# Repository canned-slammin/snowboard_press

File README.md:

# snowboard_press
 Zephyr implementation of heat and pressure controls

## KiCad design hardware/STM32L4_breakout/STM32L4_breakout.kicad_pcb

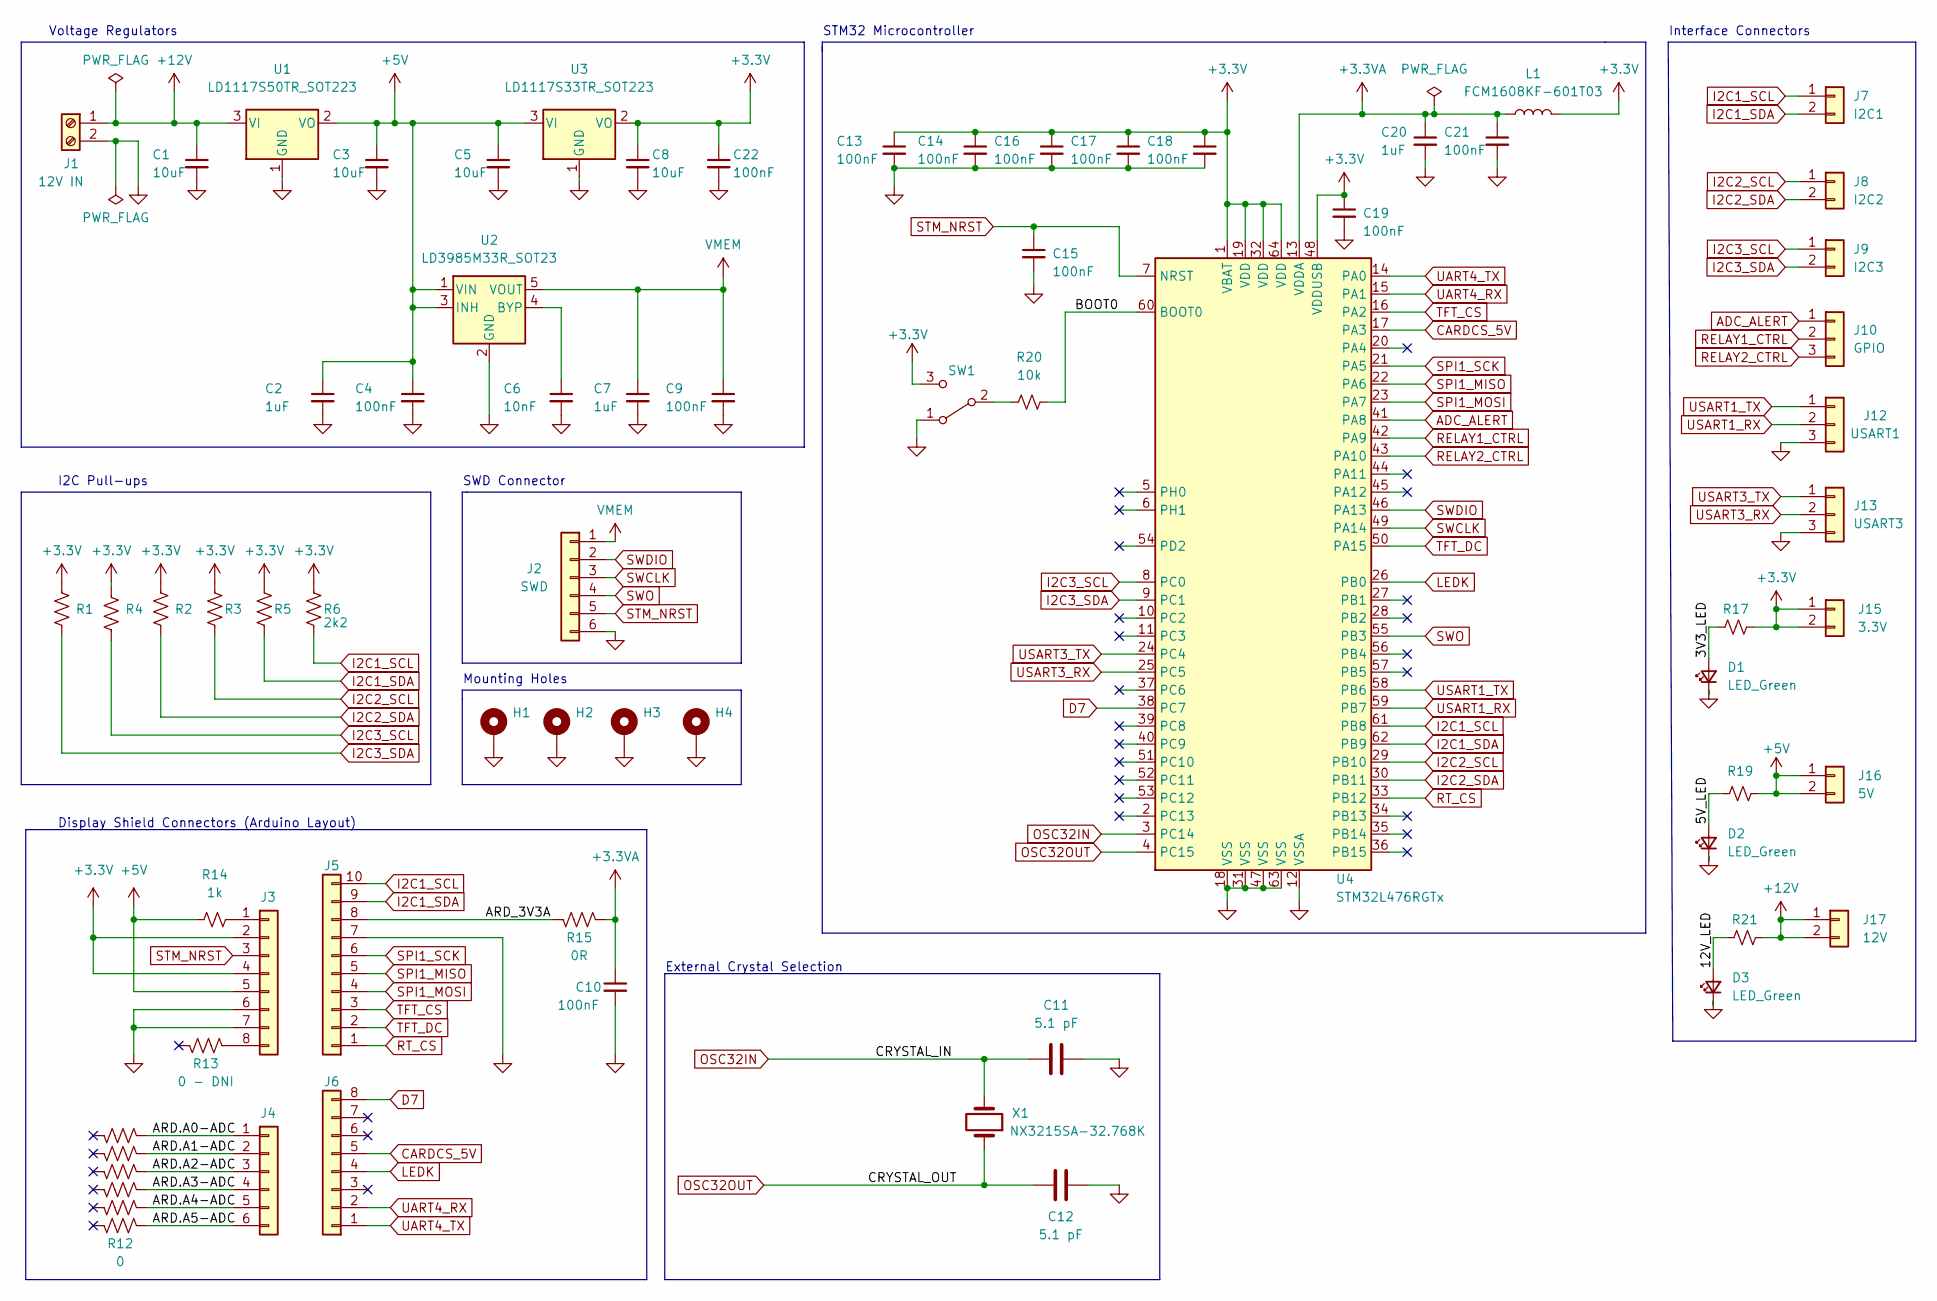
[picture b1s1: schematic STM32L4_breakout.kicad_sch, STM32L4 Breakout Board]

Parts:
C1, C3, C5, C8: 10uF; C_0805_2012Metric
C2, C7, C20: 1uF; C_0805_2012Metric
C4, C9, C10, C13, C14, C15, C16, C17, C18, C19, C21, C22: 100nF; C_0603_1608Metric
C6: 10nF; C_0603_1608Metric
C11, C12: 5.1 pF; C_0402_1005Metric
D1, D2, D3: LED_Green; LED_0603_1608Metric
H1, H2, H3, H4: MountingHole_Pad; MountingHole_3.2mm_M3_DIN965_Pad_TopOnly
J1: 12V IN; TerminalBlock_Phoenix_MKDS-1,5-2_1x02_P5.00mm_Horizontal
J2: SWD; PinHeader_1x06_P2.54mm_Vertical
J3, J6: Conn_01x08; PinSocket_1x08_P2.54mm_Vertical
J4: Conn_01x06; PinSocket_1x06_P2.54mm_Vertical
J5: Conn_01x10; PinSocket_1x10_P2.54mm_Vertical
J7: I2C1; PinHeader_1x02_P2.54mm_Vertical
J8: I2C2; PinHeader_1x02_P2.54mm_Vertical
J9: I2C3; PinHeader_1x02_P2.54mm_Vertical
J10: GPIO; PinSocket_1x03_P2.54mm_Vertical
J12: USART1; PinHeader_1x03_P2.54mm_Vertical
J13: USART3; PinHeader_1x03_P2.54mm_Vertical
J15: 3.3V; PinHeader_1x02_P2.54mm_Vertical
J16: 5V; PinHeader_1x02_P2.54mm_Vertical
J17: 12V; PinHeader_1x02_P2.54mm_Vertical
L1: FCM1608KF-601T03; L_0603_1608Metric
R1, R2, R3, R4, R5, R6: 2k2; R_0603_1608Metric
R7, R8, R9, R10, R11, R13: 0 - DNI; R_0603_1608Metric
R12: 0; R_0603_1608Metric
R14: 1k; R_0603_1608Metric
R15: 0R; R_0603_1608Metric
R17, R19, R21: 330R; R_0603_1608Metric
R20: 10k; R_0603_1608Metric
SW1: SW_SPDT; SW_SPDT_CK-JS102011SAQN
U1: LD1117S50TR_SOT223; SOT-223-3_TabPin2
U2: LD3985M33R_SOT23; SOT-23-5
U3: LD1117S33TR_SOT223; SOT-223-3_TabPin2
U4: STM32L476RGTx; LQFP-64_10x10mm_P0.5mm
X1: NX3215SA-32.768K; Crystal_SMD_3215-2Pin_3.2x1.5mm

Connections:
+3.3V: C8.1, C13.1, C14.1, C16.1, C17.1, C18.1, C19.1, C22.1, J3.2, J3.4, J15.1, J15.2, L1.2, R1.1, R2.1, R3.1, R4.1, R5.1, R6.1, R17.2, SW1.3 (C), U3.2 (VO), U4.1 (VBAT), U4.19 (VDD), U4.32 (VDD), U4.48 (VDDUSB), U4.64 (VDD)
+3.3VA: C10.1, C20.1, C21.1, L1.1, R15.1, U4.13 (VDDA)
+5V: C2.1, C3.1, C4.1, C5.1, J3.5, J16.1, J16.2, R14.1, R19.2, U1.2 (VO), U2.1 (VIN), U2.3 (INH), U3.3 (VI)
+12V: C1.1, J1.1, J17.1, J17.2, R21.2, U1.3 (VI)
/3V3_LED: D1.2 (A), R17.1
/5V_LED: D2.2 (A), R19.1
/12V_LED: D3.2 (A), R21.1
/ARD.A0-ADC: J4.1, R7.1
/ARD.A1-ADC: J4.2, R8.1
/ARD.A2-ADC: J4.3, R9.1
/ARD.A3-ADC: J4.4, R10.1
/ARD.A4-ADC: J4.5, R11.1
/ARD.A5-ADC: J4.6, R12.1
/ARD_3V3A: J5.8, R15.2
/BOOT0: R20.2, U4.60 (BOOT0)
ADC_ALERT: J10.1, U4.41 (PA8)
CARDCS_5V: J6.5, U4.17 (PA3)
D7: J6.8, U4.38 (PC7)
GND: C1.2, C2.2, C3.2, C4.2, C5.2, C6.2, C7.2, C8.2, C9.2, C10.2, C11.1, C12.1, C13.2, C14.2, C15.2, C16.2, C17.2, C18.2, C19.2, C20.2, C21.2, C22.2, D1.1 (K), D2.1 (K), D3.1 (K), H1.1, H2.1, H3.1, H4.1, J1.2, J2.6, J3.6, J3.7, J5.7, J12.3, J13.3, SW1.1 (A), U1.1 (GND), U2.2 (GND), U3.1 (GND), U4.12 (VSSA), U4.18 (VSS), U4.31 (VSS), U4.47 (VSS), U4.63 (VSS)
I2C1_SCL: J5.10, J7.1, R6.2, U4.61 (PB8)
I2C1_SDA: J5.9, J7.2, R5.2, U4.62 (PB9)
I2C2_SCL: J8.1, R3.2, U4.29 (PB10)
I2C2_SDA: J8.2, R2.2, U4.30 (PB11)
I2C3_SCL: J9.1, R4.2, U4.8 (PC0)
I2C3_SDA: J9.2, R1.2, U4.9 (PC1)
LEDK: J6.4, U4.26 (PB0)
unnamed: C6.1, U2.4 (BYP)
unnamed: J3.1, R14.2
unnamed: J3.8, R13.1
unnamed: R20.1, SW1.2 (B)
OSC32IN: C11.2, U4.3 (PC14), X1.2
OSC32OUT: C12.2, U4.4 (PC15), X1.1
RELAY1_CTRL: J10.2, U4.42 (PA9)
RELAY2_CTRL: J10.3, U4.43 (PA10)
RT_CS: J5.1, U4.33 (PB12)
SPI1_MISO: J5.5, U4.22 (PA6)
SPI1_MOSI: J5.4, U4.23 (PA7)
SPI1_SCK: J5.6, U4.21 (PA5)
STM_NRST: C15.1, J2.5, J3.3, U4.7 (NRST)
SWCLK: J2.3, U4.49 (PA14)
SWDIO: J2.2, U4.46 (PA13)
SWO: J2.4, U4.55 (PB3)
TFT_CS: J5.3, U4.16 (PA2)
TFT_DC: J5.2, U4.50 (PA15)
UART4_RX: J6.2, U4.15 (PA1)
UART4_TX: J6.1, U4.14 (PA0)
USART1_RX: J12.2, U4.59 (PB7)
USART1_TX: J12.1, U4.58 (PB6)
USART3_RX: J13.2, U4.25 (PC5)
USART3_TX: J13.1, U4.24 (PC4)
VMEM: C7.1, C9.1, J2.1, U2.5 (VOUT)

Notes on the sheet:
Voltage Regulators
Interface Connectors
STM32 Microcontroller
External Crystal Selection
Display Shield Connectors (Arduino Layout)
Mounting Holes
I2C Pull-ups
SWD Connector

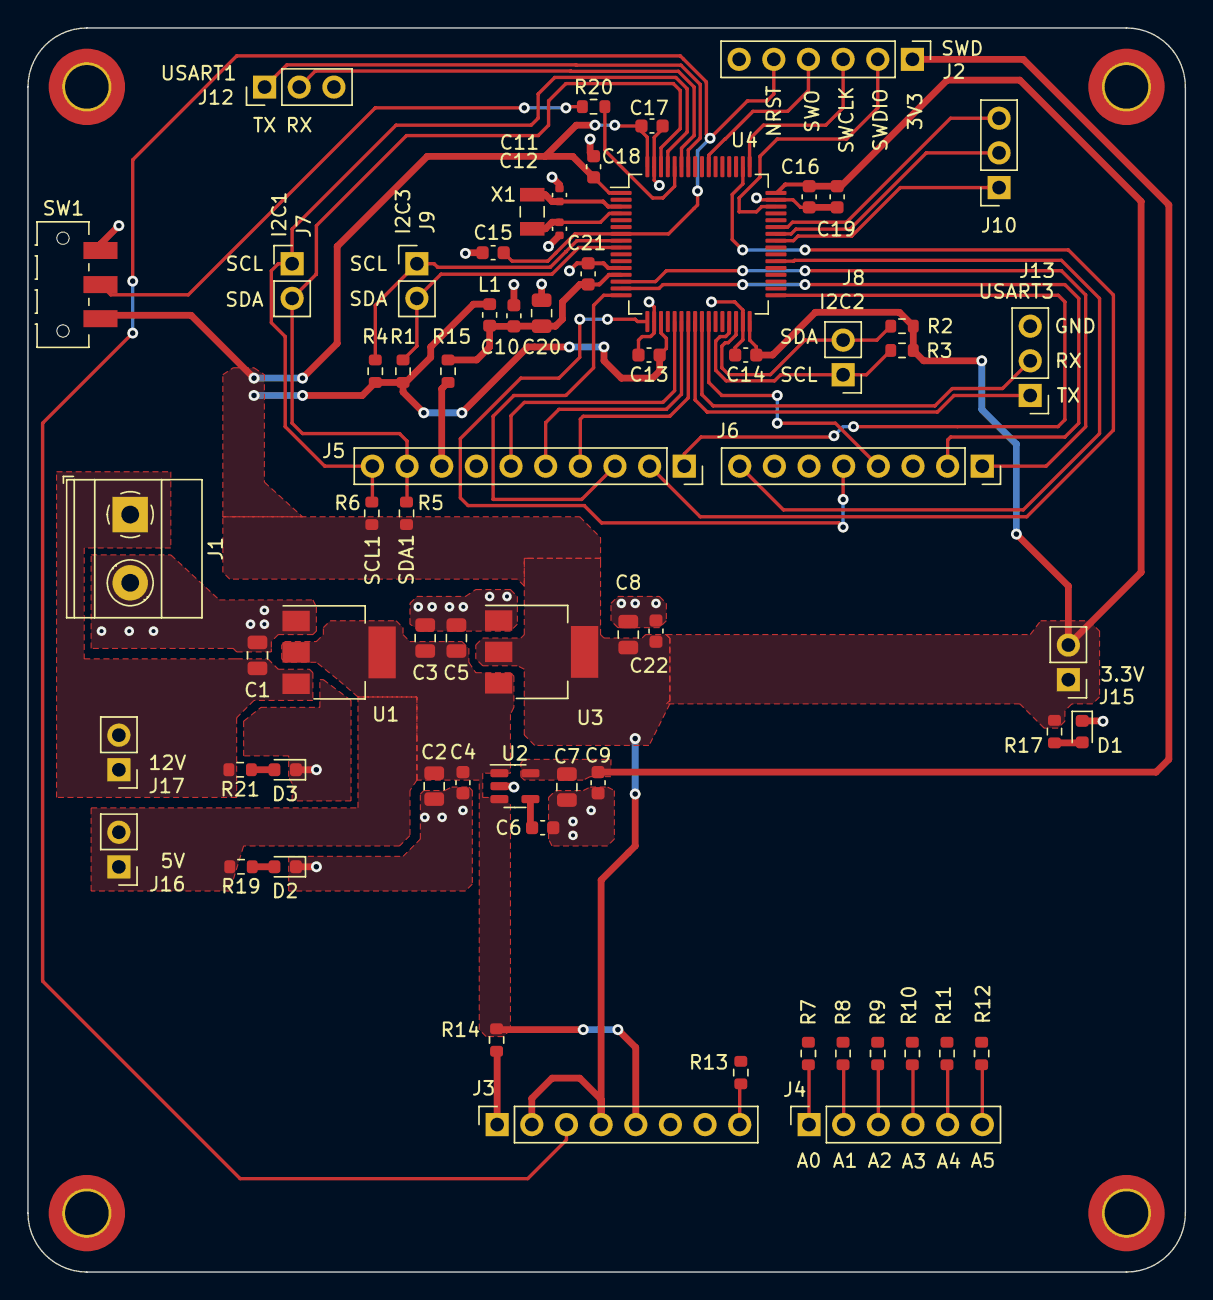
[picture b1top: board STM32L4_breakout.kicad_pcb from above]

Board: 2 copper layers, 84.8 x 91.2 mm, 70 parts (0 on the bottom side), 51 nets.

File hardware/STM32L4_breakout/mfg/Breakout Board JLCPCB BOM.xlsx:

Comment | Designator | Footprint | JLCPCB Part #
10uF | C1, C3, C5, C8 | Capacitor_SMD:C_0805_2012Metric | C1713
1uF | C2, C7, C20 | Capacitor_SMD:C_0805_2012Metric | C376925
100nF | C4, C9, C10, C13, C14, C15, C16, C17, C18, C19, C21, C22 | Capacitor_SMD:C_0603_1608Metric | C6119867
10nF | C6 | Capacitor_SMD:C_0603_1608Metric | C7503504
5.1 pF | C11, C12 | Capacitor_SMD:C_0402_1005Metric | C60220
LED_Green | D1, D2, D3 | LED_SMD:LED_0603_1608Metric | C22371297
FCM1608KF-601T03 | L1 | Inductor_SMD:L_0603_1608Metric | C141723
2k2 | R1, R2, R3, R4, R5, R6 | Resistor_SMD:R_0603_1608Metric | C4190
1k | R14 | Resistor_SMD:R_0603_1608Metric | C22764
383.0 | R17, R19, R21 | Resistor_SMD:R_0603_1608Metric | C12976
10k | R20 | Resistor_SMD:R_0603_1608Metric | C15401
JS102011SAQN | SW1 | Button_Switch_SMD:SW_SPDT_CK-JS102011SAQN | C221660
 | U1 | Package_TO_SOT_SMD:SOT-223-3_TabPin2 | C134077
LD3985M33R_SOT23 | U2 | Package_TO_SOT_SMD:SOT-23-5 | C46243
LD1117S33TR_SOT223 | U3 | Package_TO_SOT_SMD:SOT-223-3_TabPin2 | C86781
STM32L476RGTx | U4 | Package_QFP:LQFP-64_10x10mm_P0.5mm | C74797
NX3215SA-32.768K | X1 | Crystal:Crystal_SMD_3215-2Pin_3.2x1.5mm | C156244

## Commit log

2025-03-12 added windows vs code workspace
2025-03-12 started project idea doc, added empty kicad files
2025-03-12 added kicad for stm32l4 breakout
2025-03-19 added blank block diagram file for hardware
2025-03-19 1st draft of sw req's, added space for hw req's
2025-03-19 1st draft of hw req's
2025-03-21 system arch 1st draft
2025-03-21 Started hardware block diagram
2025-03-23 hw block diagaram WIP
2025-03-24 hw block diagram 1st draft
2025-03-24 state diagram WIP
2025-03-26 updated block diagram, breakout schematic WIP
2025-03-26 breakout board schematic WIP
2025-04-01 updated gitignore, pdf
2025-04-19 annotated breakout board schematic
2025-04-19 breakout schematic passes ERC
2025-04-30 breakout schematic review WIP
2025-05-01 breakout board schematic review complete
2025-05-02 selected packages
2025-05-06 breakout board PCB layout WIP
2025-05-12 breakout board layout WIP
2025-05-15 breakout board pcb layout WIP - ready for outline
2025-05-22 created PCB outline
2025-05-22 minor tweaks
2025-05-23 routed mcu caps and clock - SPI lines need move
2025-05-27 re-arrange pcb layout for SPI lines WIP
2025-05-28 re-drew outline based on SPI move
2025-05-28 routed SPI lines
2025-05-29 routed SWD on breakout board
2025-05-29 breakout board signal routing WIP
2025-05-30 breakout board signal trace layout WIP
2025-05-30 added pullups to I2C3
2025-05-30 breakout board I2C2 routing WIP
2025-06-04 moved GPIO signals on schematic
2025-06-04 signal routing complete
2025-06-04 breakout board power routing WIP
2025-06-04 breakout board re-routed D7
2025-06-04 d7 change to schematic
2025-06-06 added pwr indicator LEDs
2025-06-09 Breakout Board PCB power routing WIP
2025-06-11 breakout routing done, open ERC warnings
2025-06-11 breakout board routing complete, ERC done
2025-06-12 generated mfg files
2025-06-12 updated boot switch footprint
2025-06-16 updated switch in BOM
2025-06-16 removed 0ohm osc resistors
2025-06-16 added breakout board JLCPCB BOM
2025-06-17 updated gerber zip
2025-06-17 I frigged up some GPIOs
2025-06-17 leaving notes about my silliness
2025-06-18 started zephyr dts and other files
2025-06-19 dts supporting files added to board folder
2025-06-19 first draft bringing over dts info from disco board
2025-06-20 app skeleton WIP
2025-06-20 dts compiles from within zephyr repo
2025-06-20 removed pwm and adc shell kconfigs
2025-06-20 pcb works from repo (command line def, task maybe)
2025-06-20 added mfg files for modules
2025-06-20 added (untested) openOCD cfg file to workspace
2025-06-20 added (untested) debug configs for jlink
2025-06-25 added notes on PCBA result
2025-06-27 hw config with display compiles
2025-06-27 LVGL example compiles (untested on HW)
2025-06-27 added hw note, also display boots
2025-06-27 display insta post WIP - count does not enumerate
2025-06-30 updated beer sample (needs test)
2025-06-30 subsystem testing on touchscreen WIP
2025-07-01 buttons and alert show up on screen
2025-07-01 subsystem test interface WIP
2025-07-02 cleanup example code, add TODOs
2025-07-02 cleaning up includes on subsys test
2025-07-02 message q for subsys test WIP
2025-07-07 subsystem test GUI WIP
2025-07-08 gpio test compiles, needs hw test
2025-07-10 GPIO testing WIP
2025-07-10 toggling relays works
2025-07-10 idk how friggin strings work
2025-07-10 basic GPIO subsystem testing works
2025-07-10 cleanup
2025-07-10 BROKEN COMMIT (gpio output not working)
2025-07-14 Revert "BROKEN COMMIT (gpio output not working)"
    This reverts commit d02fa6a43e08c6bcb1bd703bd06e8a33ad5e1998.
2025-07-14 Revert "cleanup"
    This reverts commit 1361b2346bb29efecfe2ac08a16e44666c68d0bf.
2025-07-14 update ADS model
2025-07-14 updated notes and block diagram
2025-08-04 modbus setup code compiles
2025-08-05 modbus console commands WIP (needs compile)
2025-08-06 shell outline compiles
2025-08-06 removed de-gpios, commit still does not boot
2025-08-06 fixed prj.conf typo, modbus outline works in shell
2025-08-07 client interface recognized by shell, not verified if matching main
2025-08-11 client interface matches main and console (0)
2025-08-12 modbus write reg cmd compiles
2025-08-12 read_reg and write_reg rtu_client over uart4
2025-08-12 moved modbus serial to USART3
2025-08-22 modbus read reg fp compiles, runs server-less
2025-08-25 added read_reg_fp, needs hw test
2025-09-19 fp sorta verified on rtu_server example
2025-10-09 removed modbus from project :(
2025-10-09 outline for testing bacnet comms
2025-10-10 UART test interface WIP
2025-10-11 builds but crashes on flash
2025-10-13 HEY, AT LEAST IT BOOTS
2025-10-13 pinpointed where it's crashing on boot
2025-10-13 still doesn't work
2025-10-16 fixed jlink debugger, got stuck on UART. try echo sample again
2025-10-17 left foreboding TODO
2025-10-20 uart example works on main with EVERYTHING else commented out
2025-10-21 echo bot (sloppily) intergrated into system test loop
2025-10-27 successfully recieved 16-byte array over UART3
2025-10-30 added TODOs for BACNet messaging tests
2025-11-03 just more TODOs for bacnet testing
